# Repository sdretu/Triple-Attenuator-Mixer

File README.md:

Triple-Attenuator-Mixer
=======================

A eurorack modular synthesizer simple mixer and attenuator module.

This work is made available under a Creative Commons CC BY SA license:
http://creativecommons.org/licenses/by-sa/3.0/

You are free:

- to Share — to copy, distribute and transmit the work
- to Remix — to adapt the work
- to make commercial use of the work
		
Under the following conditions:

- Attribution — You must attribute the work in the manner specified by the author or licensor (but not in any way that suggests that they endorse you or your use of the work).
- Share Alike — If you alter, transform, or build upon this work, you may distribute the resulting work only under the same or similar license to this one.

With the understanding that:

Waiver — Any of the above conditions can be waived if you get permission from the copyright holder.

Public Domain — Where the work or any of its elements is in the public domain under applicable law, that status is in no way affected by the license.

Other Rights — In no way are any of the following rights affected by the license:
- Your fair dealing or fair use rights, or other applicable copyright exceptions and limitations;
- The author's moral rights;
- Rights other persons may have either in the work itself or in how the work is used, such aspublicity or privacy rights.
- Notice — For any reuse or distribution, you must make clear to others the license terms of this work. The best way to do this is with a link to this web page.

CC BY SA 2012 Julien Nicault

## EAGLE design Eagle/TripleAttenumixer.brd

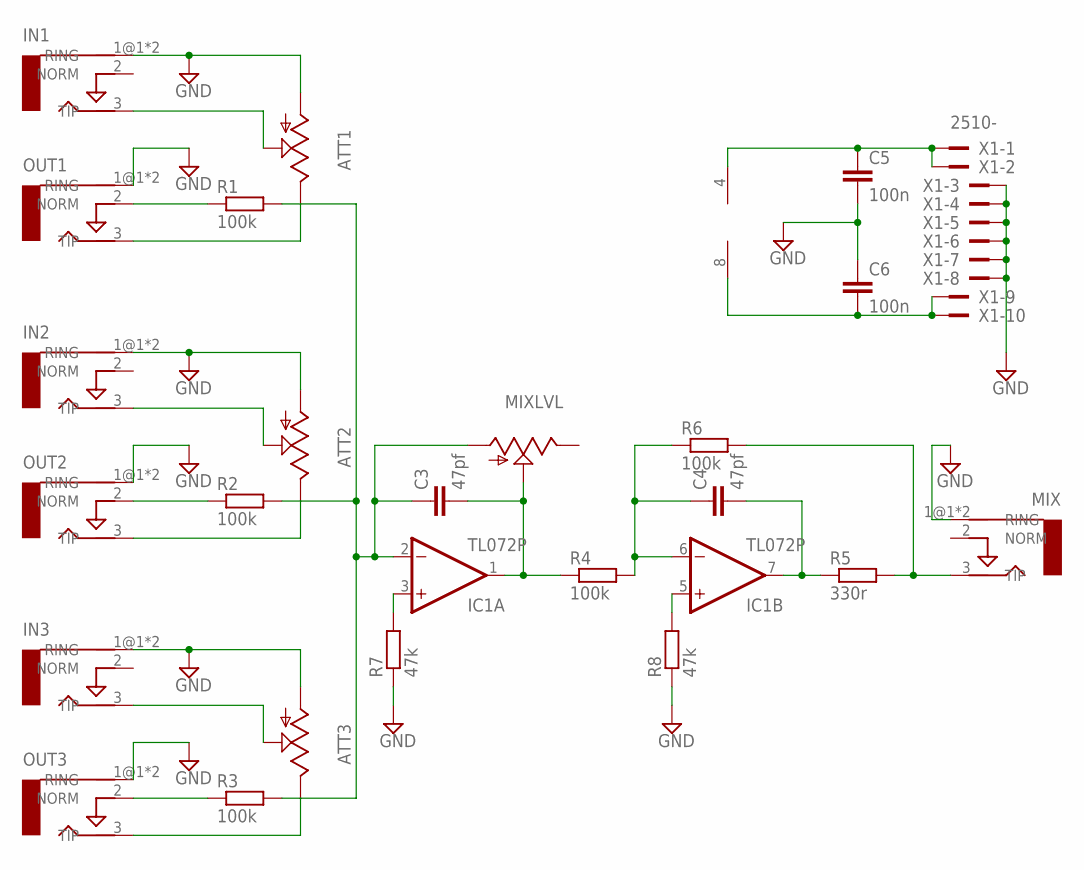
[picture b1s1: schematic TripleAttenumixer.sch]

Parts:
ATT1, ATT2, ATT3: US-EVUF2A; EVUF
C3, C4: 47pf; C025_050-025X075
C5, C6: 100n; C025_050-025X075; MPN 100NHG000B
IC1: TL072P; DIL08
IN1, IN2, IN3: AUDIO-JACKERTHENVAR; ERTHENVAR-JACK
MIX: AUDIO-JACKERTHENVAR; ERTHENVAR-JACK
MIXLVL: US-EVUF2A; EVUF
OUT1, OUT2, OUT3: AUDIO-JACKERTHENVAR; ERTHENVAR-JACK
R1, R2, R3, R4, R6: 100k; 0207/7
R5: 330r; 0207/7
R7, R8: 47k; 0207/7
X1: 2510-; PAK100/2500-10; MPN N2510-6002RB.

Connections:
GND: ATT1.1 (A), ATT2.1 (A), ATT3.1 (A), C5.2, C6.1, IN1.1@1 (RING), IN1.1@2 (RING), IN2.1@1 (RING), IN2.1@2 (RING), IN3.1@1 (RING), IN3.1@2 (RING), MIX.1@1 (RING), MIX.1@2 (RING), OUT1.1@1 (RING), OUT1.1@2 (RING), OUT2.1@1 (RING), OUT2.1@2 (RING), OUT3.1@1 (RING), OUT3.1@2 (RING), R7.1, R8.1, X1.3, X1.4, X1.5, X1.6, X1.7, X1.8
unnamed: ATT1.2 (S), IN1.3 (TIP)
unnamed: ATT1.3 (E), OUT1.3 (TIP)
unnamed: ATT2.2 (S), IN2.3 (TIP)
unnamed: ATT2.3 (E), OUT2.3 (TIP)
unnamed: ATT3.2 (S), IN3.3 (TIP)
unnamed: ATT3.3 (E), OUT3.3 (TIP)
unnamed: OUT1.2 (NORM), R1.1
unnamed: OUT2.2 (NORM), R2.1
unnamed: OUT3.2 (NORM), R3.1
unnamed: C3.1, IC1.2 (-IN), MIXLVL.1 (A), R1.2, R2.2, R3.2
unnamed: C3.2, IC1.1 (OUT), MIXLVL.2 (S), R4.1
unnamed: C4.2, IC1.7 (OUT), R5.1
unnamed: IC1.3 (+IN), R7.2
unnamed: IC1.5 (+IN), R8.2
unnamed: MIX.3 (TIP), R5.2, R6.2
unnamed: C4.1, IC1.6 (-IN), R4.2, R6.1
unnamed: C5.1, IC1.4 (V-), X1.1, X1.2
unnamed: C6.2, IC1.8 (V+), X1.9, X1.10

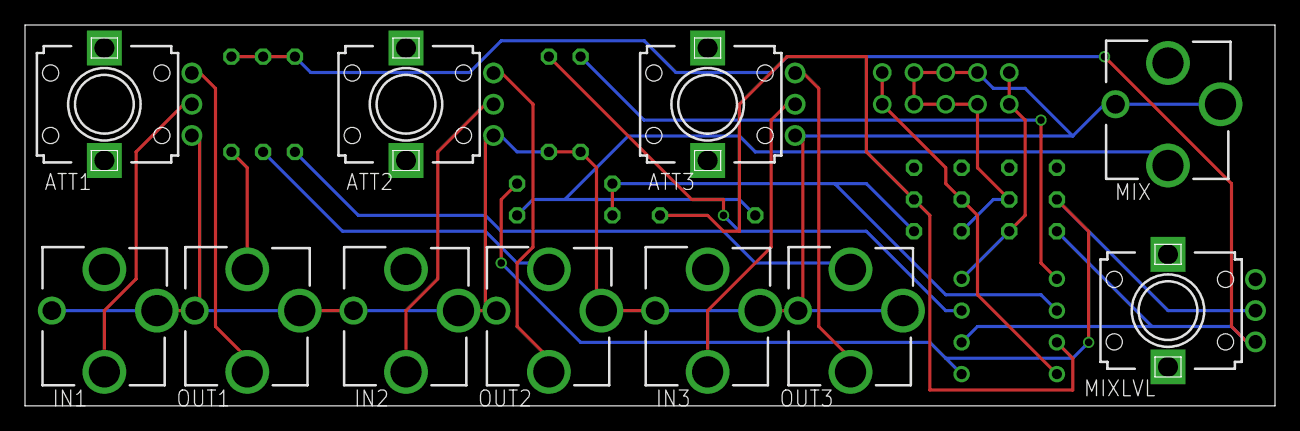
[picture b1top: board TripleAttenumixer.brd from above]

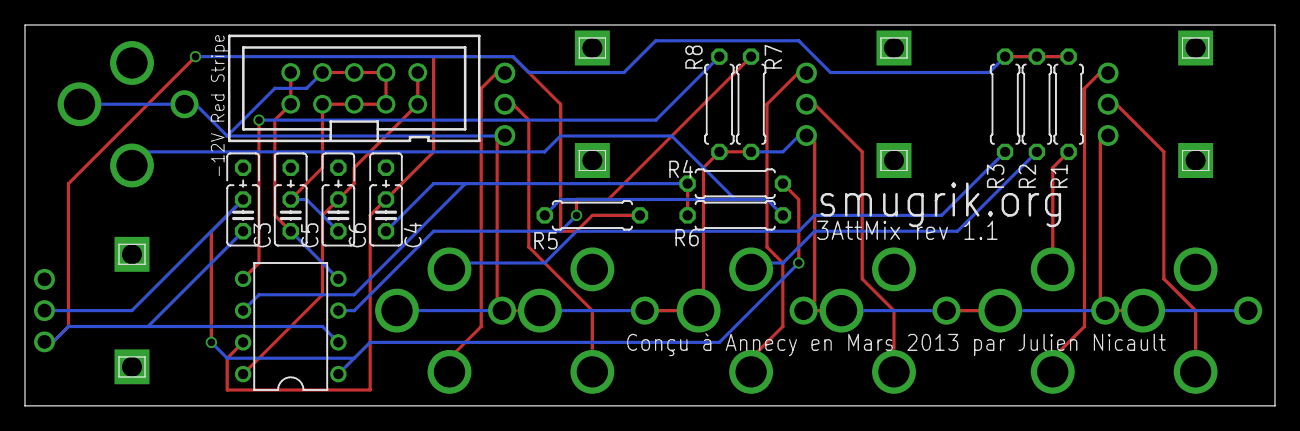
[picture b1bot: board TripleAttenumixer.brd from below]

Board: 2 copper layers, 100.0 x 30.5 mm, 25 parts (14 on the bottom side), 19 nets.

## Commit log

2013-06-27 Update README.md
    Added CC-by-SA
2013-06-27 Added eagle board and schematics files and Front Panel Designer files
2013-06-27 Revert "Added eagle board and schematics files"
    This reverts commit 396ebd0729cceece7a30ca9225194db603fa9607.
2013-06-27 Eagle and FPD
    Added eagle .brd and .sch files.
    Added front panel designer .fpd file
2013-11-10 Added frontpanel for fitting wired alpha pots
2013-11-25 Updated FPD file for alphapots panel
2013-11-25 ignore .bak files
2013-11-26 Modified some of the engraving
2013-11-26 Lines longer
2014-10-12 added .DS_Store to gitignore
2015-04-09 Fixed small layout glitch with text on the silkscreen layer
